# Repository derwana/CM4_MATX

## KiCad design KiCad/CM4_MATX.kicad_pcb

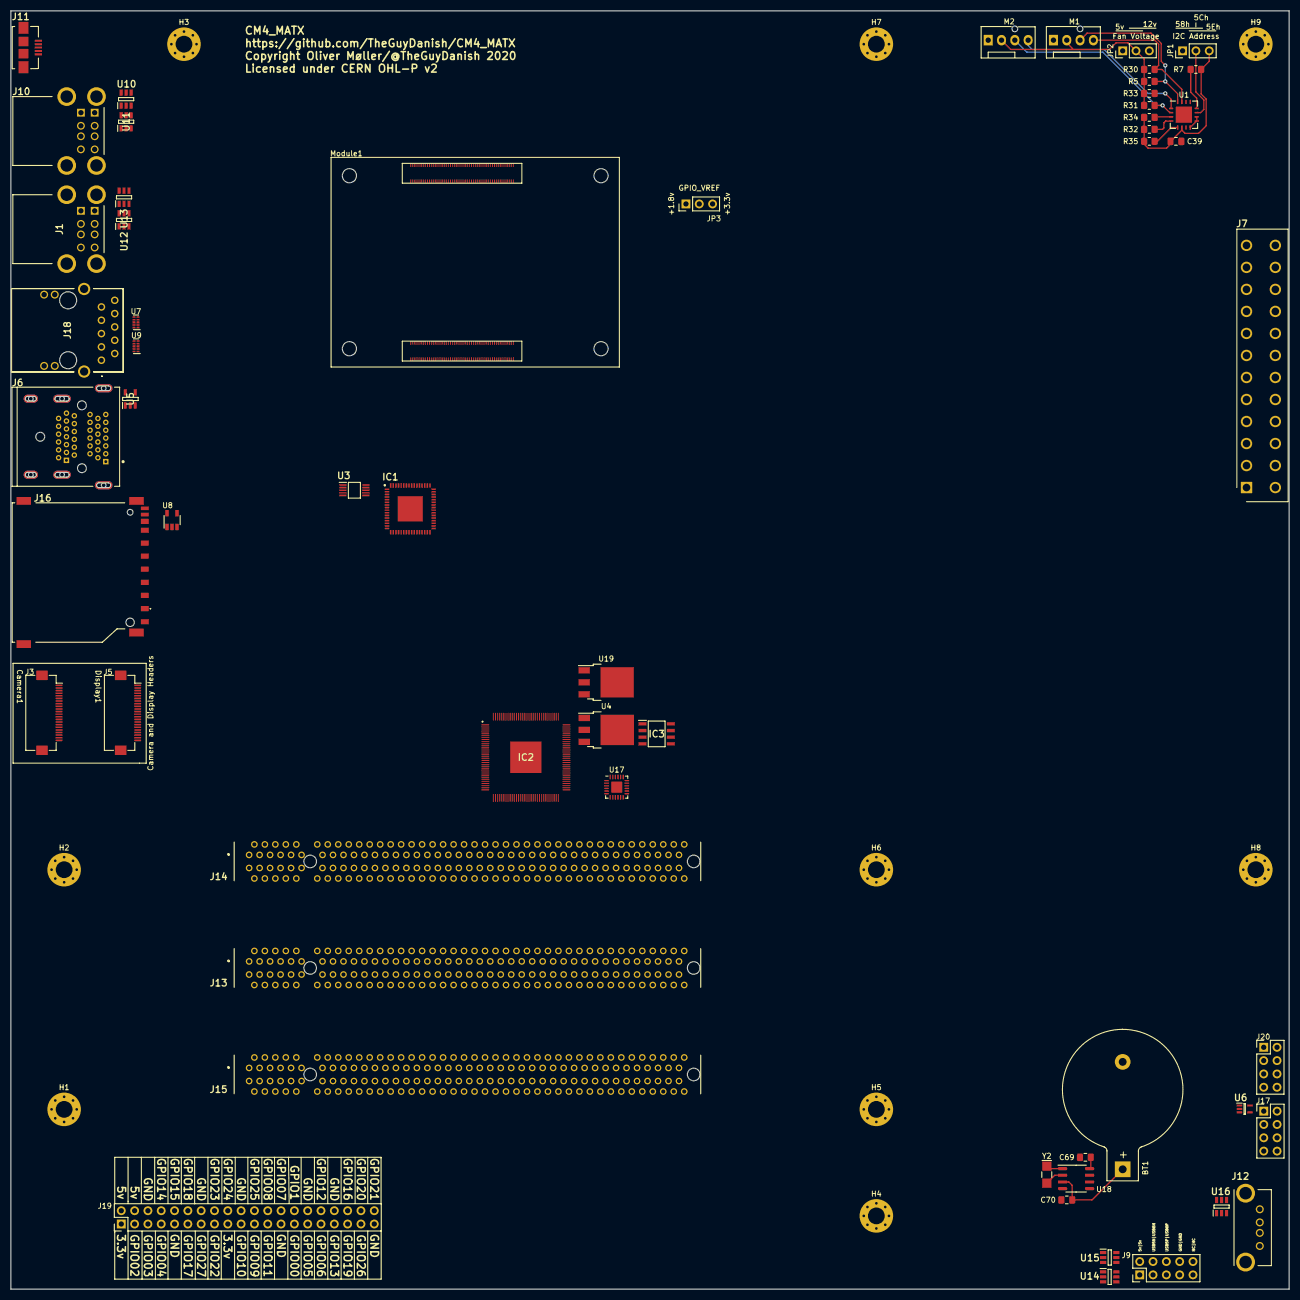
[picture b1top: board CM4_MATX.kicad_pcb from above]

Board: 2 copper layers, 243.8 x 243.8 mm, 66 parts (0 on the bottom side), 204 nets.

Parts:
BT1: Battery_Cell; BatteryHolder_Keystone_103_1x20mm
C39: C0.1u; C_0805_2012Metric_Pad1.18x1.45mm_HandSolder
C69, C70: C100n; C_0805_2012Metric_Pad1.18x1.45mm_HandSolder
H1, H2, H3, H4, H5, H6, H7, H8, H9: MountingHole; MountingHole_3.2mm_M3_Pad_Via
IC1: USB2517-JZX; QFN50P900X900X100-65N-D
IC2: PI7C9X2G404SLBFDE; QFP40P1600X1600X160-129N
IC3: M24C04-RMN6TP; SOIC127P600X175-8N
J1, J10: 72309-8014BLF; 723098014BLF
J3, J5: Conn_01x22_Female; Hirose_FH12-22S-0.5SH_1x22-1MP_P0.50mm_Horizontal
J6: 1888811-1; TE_1888811-1
J7: 39-28-1243; SHDR24W125P550X420_2X12_5160X960X1310P
J9: Conn_02x05_Odd_Even; PinHeader_2x05_P2.54mm_Vertical
J11: 10104110-0001LF; 101041100001LF
J12: SS-52100-002; SS52100002
J13, J14, J15: PCIe_x16; 10018783-10113TLF
J16: GSD090012SEU
J17, J20: Conn_02x04_Odd_Even; PinHeader_2x04_P2.54mm_Vertical
J18: ARJM11C7-502-AB-ER2-T; ARJM11C7502ABER2T
J19: Conn_02x20_Odd_Even; PinHeader_2x20_P2.54mm_Vertical
JP1, JP2, JP3: Jumper_3_Open; PinHeader_1x03_P2.54mm_Vertical
M1, M2: Fan_CPU_4pin; FanPinHeader_1x04_P2.54mm_Vertical
Module1: ComputeModule4-CM4; rpiCM4
R5, R7, R30, R31, R32, R33, R34, R35: R4.7k; R_0805_2012Metric_Pad1.20x1.40mm_HandSolder
U1: MAX6639ATE+; TQFN-16-1EP_5x5mm_P0.8mm_EP3.1x3.1mm
U3: FSUSB42MUX; SOP50P490X110-10N
U4, U19: AP7363-10D; TO-252-3_TabPin2
U5: AP2822CKETR-G1; SOT95P282X145-5N
U6: 74LVC1G07GW; SOT65P212X110-5N
U7, U9: TPD4EUSB30; USON-10_2.5x1.0mm_P0.5mm
U8: RT9742GGJ5; TSOT-23-5
U10, U11, U12, U13, U14, U15, U16: MIC2019YM6-TR; SOT95P280X145-6N
U17: TCA9548ARGER; Texas_RGE0024C_EP2.1x2.1mm
U18: PCF85263AT; SO-8_3.9x4.9mm_P1.27mm
Y2: Crystal; Crystal_SMD_MicroCrystal_CC7V-T1A-2Pin_3.2x1.5mm_HandSolder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

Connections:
+3.3VA: J13.B10, J14.B10, J15.B10
+3.3VP: J13.A9, J13.A10, J13.B8, J14.A9, J14.A10, J14.B8, J15.A9, J15.A10, J15.B8, U17.21
+3V3: C39.1, IC1.5, IC1.10, IC1.24, IC1.52, IC1.57, IC1.64, J3.22, J5.22, J7.2, J7.12, J7.13, JP1.3, R7.2, R32.2, R34.2, R35.2, U1.6, U3.1
+12P: J13.A2, J13.A3, J13.B1, J13.B2, J13.B3, J14.A2, J14.A3, J14.B1, J14.B2, J14.B3, J15.A2, J15.A3, J15.B1, J15.B2, J15.B3
+12V: J7.10, J7.11, JP2.3
/+5v: C69.1, J7.4, J7.6, J7.21, J7.22, J7.23, J19.2, J19.4, JP2.1, Module1.77, Module1.79, Module1.81, Module1.83, Module1.85, Module1.87, U5.4, U5.5, U10.1, U11.1, U12.1, U13.1, U14.1, U15.1, U16.1, U18.8
/CAM_GPIO: J3.17, Module1.97
/CM4_GPIO/+1.8v: JP3.1, Module1.88, Module1.90
/CM4_GPIO/+3.3v: J18.L1, J18.L3, J19.1, J19.17, JP3.3, Module1.84, Module1.86, U6.5, U8.5
/CM4_GPIO/BT_nDis: J20.3, Module1.91
/CM4_GPIO/EEPROM_nWP: J20.7, Module1.20
/CM4_GPIO/GPIO2: J19.3, Module1.58
/CM4_GPIO/GPIO3: J19.5, Module1.56
/CM4_GPIO/GPIO4: J19.7, Module1.54
/CM4_GPIO/GPIO5: J19.29, Module1.34
/CM4_GPIO/GPIO6: J19.31, Module1.30
/CM4_GPIO/GPIO7: J19.26, Module1.37
/CM4_GPIO/GPIO8: J19.24, Module1.39
/CM4_GPIO/GPIO9: J19.21, Module1.40
/CM4_GPIO/GPIO10: J19.19, Module1.44
/CM4_GPIO/GPIO11: J19.23, Module1.38
/CM4_GPIO/GPIO12: J19.32, Module1.31
/CM4_GPIO/GPIO13: J19.33, Module1.28
/CM4_GPIO/GPIO14: J19.8, Module1.55
/CM4_GPIO/GPIO15: J19.10, Module1.51
/CM4_GPIO/GPIO16: J19.36, Module1.29
/CM4_GPIO/GPIO17: J19.11, Module1.50
/CM4_GPIO/GPIO18: J19.12, Module1.49
/CM4_GPIO/GPIO19: J19.35, Module1.26
/CM4_GPIO/GPIO20: J19.38, Module1.27
/CM4_GPIO/GPIO21: J19.40, Module1.25
/CM4_GPIO/GPIO22: J19.15, Module1.46
/CM4_GPIO/GPIO23: J19.16, Module1.47
/CM4_GPIO/GPIO24: J19.18, Module1.45
/CM4_GPIO/GPIO25: J19.22, Module1.41
/CM4_GPIO/GPIO26: J19.37, Module1.24
/CM4_GPIO/GPIO27: J19.13, Module1.48
/CM4_GPIO/PI_nLED_ACT: J17.3, Module1.21
/CM4_GPIO/RUN_PG: J17.7, Module1.92
/CM4_GPIO/SD_CLK: J16.5, Module1.57
/CM4_GPIO/SD_CMD: J16.2, Module1.62
/CM4_GPIO/SD_DAT0: J16.7, Module1.63
/CM4_GPIO/SD_DAT1: J16.8, Module1.67
/CM4_GPIO/SD_DAT2: J16.9, Module1.69
/CM4_GPIO/SD_DAT3: J16.1, Module1.61
/CM4_GPIO/SD_DET: J16.10, Module1.76
/CM4_GPIO/SD_PWR: J16.4, U8.1
/CM4_GPIO/SD_PWR_ON: Module1.75, U8.4
/CM4_GPIO/TRD0_N: J18.2, Module1.10, U7.4
/CM4_GPIO/TRD0_P: J18.1, Module1.12, U7.5
/CM4_GPIO/TRD1_N: J18.4, Module1.6, U7.2
/CM4_GPIO/TRD1_P: J18.3, Module1.4, U7.1
/CM4_GPIO/TRD2_N: J18.8, Module1.9, U9.4
/CM4_GPIO/TRD2_P: J18.7, Module1.11, U9.5
/CM4_GPIO/TRD3_N: J18.10, Module1.5, U9.2
/CM4_GPIO/TRD3_P: J18.9, Module1.3, U9.1
/CM4_GPIO/WL_nDis: J20.1, Module1.89
/CM4_GPIO/nPWR_LED: Module1.95, U6.2
/CM4_GPIO/nRPIBOOT: J20.5, Module1.93
/CM4_HighSpeed/CAM1_C_N: J3.8, Module1.127
/CM4_HighSpeed/CAM1_C_P: J3.9, Module1.129
/CM4_HighSpeed/CAM1_D0_N: J3.2, Module1.115
/CM4_HighSpeed/CAM1_D0_P: J3.3, Module1.117
/CM4_HighSpeed/CAM1_D1_N: J3.5, Module1.121
/CM4_HighSpeed/CAM1_D1_P: J3.6, Module1.123
/CM4_HighSpeed/CAM1_D2_N: J3.11, Module1.133
/CM4_HighSpeed/CAM1_D2_P: J3.12, Module1.135
/CM4_HighSpeed/CAM1_D3_N: J3.14, Module1.139
/CM4_HighSpeed/CAM1_D3_P: J3.15, Module1.141
/CM4_HighSpeed/DSI1_C_N: J5.8, Module1.187
/CM4_HighSpeed/DSI1_C_P: J5.9, Module1.189
/CM4_HighSpeed/DSI1_D0_N: J5.2, Module1.175
/CM4_HighSpeed/DSI1_D0_P: J5.3, Module1.177
/CM4_HighSpeed/DSI1_D1_N: J5.5, Module1.181
/CM4_HighSpeed/DSI1_D1_P: J5.6, Module1.183
/CM4_HighSpeed/DSI1_D2_N: J5.11, Module1.193
/CM4_HighSpeed/DSI1_D2_P: J5.12, Module1.195
/CM4_HighSpeed/DSI1_D3_N: J5.14, Module1.194
/CM4_HighSpeed/DSI1_D3_P: J5.15, Module1.196
/CM4_HighSpeed/HDMI0_CEC: J6.AP13, Module1.151
/CM4_HighSpeed/HDMI0_CK_N: J6.AP12, Module1.190
/CM4_HighSpeed/HDMI0_CK_P: J6.AP10, Module1.188
/CM4_HighSpeed/HDMI0_D0_N: J6.AP9, Module1.184
/CM4_HighSpeed/HDMI0_D0_P: J6.AP7, Module1.182
/CM4_HighSpeed/HDMI0_D1_N: J6.AP6, Module1.178
/CM4_HighSpeed/HDMI0_D1_P: J6.AP4, Module1.176
/CM4_HighSpeed/HDMI0_D2_N: J6.AP3, Module1.172
/CM4_HighSpeed/HDMI0_D2_P: J6.AP1, Module1.170
/CM4_HighSpeed/HDMI0_HOTPLUG: J6.AP19, Module1.153
/CM4_HighSpeed/HDMI0_SCL: J6.AP15, Module1.200
/CM4_HighSpeed/HDMI0_SDA: J6.AP16, Module1.199
/CM4_HighSpeed/HDMI1_CEC: J6.BP13, Module1.149
/CM4_HighSpeed/HDMI1_CK_N: J6.BP12, Module1.166
/CM4_HighSpeed/HDMI1_CK_P: J6.BP10, Module1.164
/CM4_HighSpeed/HDMI1_D0_N: J6.BP9, Module1.160
/CM4_HighSpeed/HDMI1_D0_P: J6.BP7, Module1.158
/CM4_HighSpeed/HDMI1_D1_N: J6.BP6, Module1.154
/CM4_HighSpeed/HDMI1_D1_P: J6.BP4, Module1.152
/CM4_HighSpeed/HDMI1_D2_N: J6.BP3, Module1.148
/CM4_HighSpeed/HDMI1_D2_P: J6.BP1, Module1.146
/CM4_HighSpeed/HDMI1_HOTPLUG: J6.BP19, Module1.143
/CM4_HighSpeed/HDMI1_SCL: J6.BP15, Module1.147
/CM4_HighSpeed/HDMI1_SDA: J6.BP16, Module1.145
/CM4_HighSpeed/HDMI_5v: J6.AP18, J6.BP18, U5.1
/CM4_HighSpeed/PCIE_CLK_N: IC2.73, Module1.112
/CM4_HighSpeed/PCIE_CLK_P: IC2.74, Module1.110
/CM4_HighSpeed/PCIE_NRST: IC2.10, Module1.109
/CM4_HighSpeed/PCIE_RX_N: IC2.123, Module1.118
/CM4_HighSpeed/PCIE_RX_P: IC2.124, Module1.116
/CM4_HighSpeed/USB2_N: Module1.103, U3.4
/CM4_HighSpeed/USB2_P: Module1.105, U3.3
/CM4_USB2_Power/HD1_5v: J10.A1, U10.6
/CM4_USB2_Power/HD2_5v: J10.B1, U11.6
/CM4_USB2_Power/HD3_5v: J1.A1, U12.6
/CM4_USB2_Power/HD4_5v: J1.B1, U13.6
/CM4_USB2_Power/HD5_5v: J9.1, U14.6
/CM4_USB2_Power/HD6_5v: J9.2, U15.6
/CM4_USB2_Power/HD7_5v: J12.1, U16.6
/CM4_USB2_Power/USB1_PWR: IC1.29, U10.3
/CM4_USB2_Power/USB2_PWR: IC1.26, U11.3
/CM4_USB2_Power/USB3_PWR: IC1.23, U12.3
/CM4_USB2_Power/USB4_PWR: IC1.20, U13.3
/CM4_USB2_Power/USB5_PWR: IC1.30, U14.3
/CM4_USB2_Power/USB6_PWR: IC1.39, U15.3
/CM4_USB2_Power/USB7_PWR: IC1.36, U16.3
/CM4_USB2_Power/nOCS1: IC1.28, U10.4
/CM4_USB2_Power/nOCS2: IC1.27, U11.4
/CM4_USB2_Power/nOCS3: IC1.22, U12.4
/CM4_USB2_Power/nOCS4: IC1.21, U13.4
/CM4_USB2_Power/nOCS5: IC1.35, U14.4
/CM4_USB2_Power/nOCS6: IC1.38, U15.4
/CM4_USB2_Power/nOCS7: IC1.37, U16.4
/FanCTRL_MAX6639/ADD: JP1.2, U1.11
/FanCTRL_MAX6639/DX: U1.8, U1.9, U1.10
/FanCTRL_MAX6639/PWM1: M1.4, R30.2, U1.15
/FanCTRL_MAX6639/PWM2: M2.4, R33.2, U1.1
/FanCTRL_MAX6639/TACH1: M1.3, R5.2, U1.16
/FanCTRL_MAX6639/TACH2: M2.3, R31.2, U1.2
/FanCTRL_MAX6639/V_FAN: JP2.2, M1.2, M2.2, R5.1, R30.1, R31.1, R33.1
/FanCTRL_MAX6639/~ALERT: R7.1, U1.12
/FanCTRL_MAX6639/~FANFAIL: R34.1, U1.3
/FanCTRL_MAX6639/~OT: R35.1, U1.5
/FanCTRL_MAX6639/~THERM: R32.1, U1.4
/GPIO_VREF: JP3.2, Module1.78
/ID_SC: J19.28, Module1.35
/ID_SD: J19.27, Module1.36
/PCIe_Subsystem/PCIE1_SMBUS_CLK: J14.B5, U17.4
/PCIe_Subsystem/PCIE1_SMBUS_DATA: J14.B6, U17.3
/PCIe_Subsystem/PCIE2_SMBUS_CLK: J13.B5, U17.6
/PCIe_Subsystem/PCIE2_SMBUS_DATA: J13.B6, U17.5
/PCIe_Subsystem/PCIE3_SMBUS_CLK: J15.B5, U17.8
/PCIe_Subsystem/PCIE3_SMBUS_DATA: J15.B6, U17.7
/PCIe_Subsystem/PCIESW_SMBUS_CLK: IC2.26, U17.2
/PCIe_Subsystem/PCIESW_SMBUS_DATA: IC2.27, U17.1
/PCIe_Subsystem/PCIE_RX_N: IC2.127, Module1.124
/PCIe_Subsystem/PCIE_RX_P: IC2.128, Module1.122
/PCIe_Subsystem/PCIe_Slot1/PCIE1_PERST: IC2.5, J14.A11
/PCIe_Subsystem/PCIe_Slot1/PCIE1_PRSNT: IC2.19, J14.B17
/PCIe_Subsystem/PCIe_Slot1/PCIE1_RX_N: IC2.101, J14.A16
/PCIe_Subsystem/PCIe_Slot1/PCIE1_RX_P: IC2.100, J14.A17
/PCIe_Subsystem/PCIe_Slot2/PCIE2_CLK_N: IC2.102, J13.A14
/PCIe_Subsystem/PCIe_Slot2/PCIE2_PERST: IC2.6, J13.A11
/PCIe_Subsystem/PCIe_Slot2/PCIE2_PRSNT: IC2.20, J13.B17
/PCIe_Subsystem/PCIe_Slot2/PCIE2_RX_N: IC2.107, J13.A17
/PCIe_Subsystem/PCIe_Slot2/PCIE2_RX_P: IC2.106, J13.A16
/PCIe_Subsystem/PCIe_Slot3/PCIE3_PERST: IC2.7, J15.A11
/PCIe_Subsystem/PCIe_Slot3/PCIE3_PRSNT: IC2.21, J15.B17
/PCIe_Subsystem/PCIe_Slot3/PCIE3_RX_N: IC2.117, J15.A17
/PCIe_Subsystem/PCIe_Slot3/PCIE3_RX_P: IC2.118, J15.A16
/PCIe_Subsystem/PCIe_Switch/+1.0v: IC2.3, IC2.23, IC2.29, IC2.31, IC2.40, IC2.55, IC2.62, IC2.65, IC2.91, IC2.99, IC2.105, IC2.108, IC2.119, IC2.125, U4.3
/PCIe_Subsystem/PCIe_Switch/+1.0vSB: IC2.13, IC2.14, U19.3
/PCIe_Subsystem/PCIe_Switch/+3.3v: IC2.1, IC2.8, IC2.49, IC2.64, IC2.79, IC2.82, IC2.84, IC2.96, IC2.113, IC3.8, U4.1
/PCIe_Subsystem/PCIe_Switch/+3.3vSB: IC2.15, U19.1
/PCIe_Subsystem/PCIe_Switch/CGND: IC2.109, IC2.112
/PCIe_Subsystem/PCIe_Switch/EECLK: IC2.70, IC3.6
/PCIe_Subsystem/PCIe_Switch/EEPD: IC2.71, IC3.5
/RTC_PCF85263A/OSCI: U18.1, Y2.1
/RTC_PCF85263A/OSCO: U18.2, Y2.2
/RTC_PCF85263A/VBAT: BT1.1, C70.1, U18.3
/SCL0: J3.20, J5.20, Module1.80, U1.13, U17.19, U18.6
/SDA0: J3.21, J5.21, Module1.82, U1.14, U17.20, U18.5
/USB2_HUB/3.3v: IC1.44, IC1.46
/USB2_HUB/HD1_N: IC1.1, J10.A2
/USB2_HUB/HD1_P: IC1.2, J10.A3
/USB2_HUB/HD2_N: IC1.3, J10.B2
/USB2_HUB/HD2_P: IC1.4, J10.B3
/USB2_HUB/HD3_N: IC1.6, J1.A2
/USB2_HUB/HD3_P: IC1.7, J1.A3
/USB2_HUB/HD4_N: IC1.8, J1.B2
/USB2_HUB/HD4_P: IC1.9, J1.B3
/USB2_HUB/HD5_N: IC1.11, J9.3
/USB2_HUB/HD5_P: IC1.12, J9.5
/USB2_HUB/HD6_N: IC1.53, J9.4
/USB2_HUB/HD6_P: IC1.54, J9.6
/USB2_HUB/HD7_N: IC1.55, J12.2
/USB2_HUB/HD7_P: IC1.56, J12.3
/USB2_HUB/USBH_N: IC1.58, U3.8
/USB2_HUB/USBH_P: IC1.59, U3.9
/USB2_HUB/USBOTG: Module1.101, U3.2
/nEXTRST: IC1.43, Module1.100
GND: BT1.2, C39.2, C69.2, C70.2, IC1.19, IC1.65, IC2.2, IC2.4, IC2.11, IC2.12, IC2.30, IC2.32, IC2.34, IC2.41, IC2.50, IC2.56, IC2.61, IC2.63, IC2.66, IC2.87, IC2.90, IC2.95, IC2.104, IC2.120, IC2.126, IC2.129, IC3.2, IC3.3, IC3.4, IC3.7, J1.A4, J1.B4, J1.MH1, J1.MH2, J1.MH3, J1.MH4, J3.1, J3.4, J3.7, J3.10, J3.13, J3.16, J3.19, J5.1, J5.4, J5.7, J5.10, J5.13, J5.16, J5.19, J6.AP2, J6.AP5, J6.AP8, J6.AP11, J6.AP17, J6.BP2, J6.BP5, J6.BP8, J6.BP11, J6.BP17, J6.SH1, J6.SH2, J6.SH3, J6.SH4, J6.SH5, J6.SH6, J7.3, J7.5, J7.7, J7.15, J7.17, J7.18, J7.19, J7.24, J9.7, J9.8, J10.A4, J10.B4, J10.MH1, J10.MH2, J10.MH3, J10.MH4, J11.5, J11.MP1, J11.MP2, J11.MP3, J11.MP4, J12.4, J12.MH1, J12.MH2, J13.A1, J13.A4, J13.A12, J13.A15, J13.A18, J13.A20, J13.A23, J13.A24, J13.A27, J13.A28, J13.A31, J13.A34, J13.A37, J13.A38, J13.A41, J13.A42, J13.A45, J13.A46, J13.A49, J13.A51, J13.A54, J13.A55, J13.A58, J13.A59, J13.A62, J13.A63, J13.A66, J13.A67, J13.A70, J13.A71, J13.A74, J13.A75, J13.A78, J13.A79, J13.A82, J13.B4, J13.B7, J13.B13, J13.B16, J13.B18, J13.B21, J13.B22, J13.B25, J13.B26, J13.B29, J13.B30, J13.B32, J13.B35, J13.B36, J13.B39, J13.B40, J13.B43, J13.B44, J13.B47, J13.B49, J13.B52, J13.B53, J13.B56, J13.B57, J13.B60, J13.B61, J13.B64, J13.B65, J13.B68, J13.B69, J13.B72, J13.B73, J13.B76, J13.B77, J13.B80, J14.A1, J14.A4, J14.A12, J14.A15, J14.A18, J14.A20, J14.A23, J14.A24, J14.A27, J14.A28, J14.A31, J14.A34, J14.A37, J14.A38, J14.A41, J14.A42, J14.A45, J14.A46, J14.A49, J14.A51, J14.A54, J14.A55, J14.A58, J14.A59, J14.A62, J14.A63, J14.A66, J14.A67, J14.A70, J14.A71, J14.A74, J14.A75, J14.A78, J14.A79, J14.A82, J14.B4, J14.B7, J14.B13, J14.B16, J14.B18, J14.B21, J14.B22, J14.B25, J14.B26, J14.B29, J14.B30, J14.B32, J14.B35, J14.B36, J14.B39, J14.B40, J14.B43, J14.B44, J14.B47, J14.B49, J14.B52, J14.B53, J14.B56, J14.B57, J14.B60, J14.B61, J14.B64, J14.B65, J14.B68, J14.B69, J14.B72, J14.B73, J14.B76, J14.B77, J14.B80, J15.A1, J15.A4, J15.A12, J15.A15, J15.A18, J15.A20, J15.A23, J15.A24, J15.A27, J15.A28, J15.A31, J15.A34, J15.A37, J15.A38, J15.A41, J15.A42, J15.A45, J15.A46, J15.A49, J15.A51, J15.A54, J15.A55, J15.A58, J15.A59, J15.A62, J15.A63, J15.A66, J15.A67, J15.A70, J15.A71, J15.A74, J15.A75, J15.A78, J15.A79, J15.A82, J15.B4, J15.B7, J15.B13, J15.B16, J15.B18, J15.B21, J15.B22, J15.B25, J15.B26, J15.B29, J15.B30, J15.B32, J15.B35, J15.B36, J15.B39, J15.B40, J15.B43, J15.B44, J15.B47, J15.B49, J15.B52, J15.B53, J15.B56, J15.B57, J15.B60, J15.B61, J15.B64, J15.B65, J15.B68, J15.B69, J15.B72, J15.B73, J15.B76, J15.B77, J15.B80, J16.3, J16.6, J16.MP1, J16.MP2, J16.MP3, J16.MP4, J17.2, J17.4, J17.6, J17.8, J18.MH1, J18.MH2, J19.6, J19.9, J19.14, J19.20, J19.25, J19.30, J19.34, J19.39, J20.2, J20.4, J20.6, J20.8, JP1.1, M1.1, M2.1, Module1.1, Module1.2, Module1.7, Module1.8, Module1.13, Module1.14, Module1.22, Module1.23, Module1.32, Module1.33, Module1.42, Module1.43, Module1.52, Module1.53, Module1.59, Module1.60, Module1.65, Module1.66, Module1.71, Module1.74, Module1.98, Module1.107, Module1.108, Module1.113, Module1.114, Module1.119, Module1.120, Module1.125, Module1.126, Module1.131, Module1.132, Module1.137, Module1.138, Module1.144, Module1.150, Module1.155, Module1.156, Module1.161, Module1.162, Module1.167, Module1.168, Module1.173, Module1.174, Module1.179, Module1.180, Module1.185, Module1.186, Module1.191, Module1.192, Module1.197, Module1.198, U1.7, U3.5, U3.10, U4.2, U5.2, U6.3, U7.3, U7.8, U8.2, U9.3, U9.8, U10.2, U11.2, U12.2, U13.2, U14.2, U15.2, U16.2, U17.9, U17.18, U17.22, U17.23, U18.4, U19.2
unnamed: J18.5, J18.6
unnamed: J11.2, U3.6
unnamed: J11.3, U3.7

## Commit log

2020-12-24 replacing connector for cm4
    with the one from the cm4io project
2020-12-28 added KiBot config
2020-12-28 added python script for converting pdf to jpg
2020-12-28 added drill and position files
2020-12-28 changed format of position file to csv
2021-01-10 added first wiring of RTC and FAN_CTRL
    widths have to be revisited

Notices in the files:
KiCad/CM4_MATX.kicad_pcb:
Copyright Oliver Møller/@TheGuyDanish 2020
Licensed under CERN OHL-P v2
